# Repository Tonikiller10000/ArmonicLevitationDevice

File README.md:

# ArmonicLevitationDevice

## Description:
<table>
  <tr>
    <td> 
      This levitation device uses an NE555 with an TC78H621FNG Dual-Bridge driver to generate a 40KHz sine wave signal witch is sent back at the rigth distance to make zones of high and low pressure in witch it can trap small objects.
    </td>
    <td>
       </td>
  </tr>
</table>

<table>
  <tr>
    <td></td>
    <td></td>
    <td></td>
  </tr>
</table>

## Schematic:

## How/where to use:
It can be powered with a 9V battery. (5-15v operating voltage range) 
Because of it`s design, multiple tipes of transmiters/transducers can be used by bending the pins. 
To use it, you can use only one board/transmitter ans a close flat surface to reflect the wave. 
For a stronger hold, you can use another transmitter connected to the SP2 pins.

> [!IMPORTANT]
> Change the distance between the transmitter1 and the surface/transmitter2 to create the nodes and antinodes for the project to work.

<table>
  <tr>
    <td> 
    This king of technology, can be used in medical industry to observe and experiment with liquids without making contact with them.</td>
    <td></td>
  </tr>
</table>

## Links:
- TC78H621FNG datasheet (Dual-Bridge driver): https://toshiba.semicon-storage.com/info/TC78H621FNG_datasheet_en_20170410.pdf?did=57992&prodName=TC78H621FNG
- 78L05 datasheet (voltage regulator): https://www.sparkfun.com/datasheets/Components/LM7805.pdf
- NE555 datasheet (timer): https://pdf1.alldatasheet.com/datasheet-pdf/view/17972/PHILIPS/NE555.html
- Ultrasonic transducer: https://www.murata.com/-/media/webrenewal/products/sensor/ultrasonic/open/datasheet_maopn.ashx
- general transducers: https://tecsho.com/Download/Download/126816/fp

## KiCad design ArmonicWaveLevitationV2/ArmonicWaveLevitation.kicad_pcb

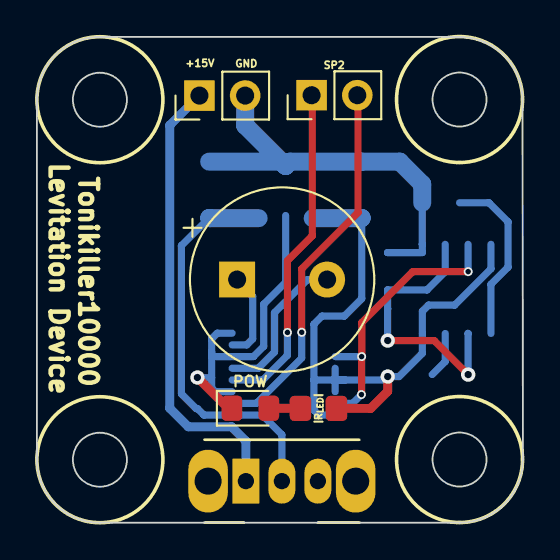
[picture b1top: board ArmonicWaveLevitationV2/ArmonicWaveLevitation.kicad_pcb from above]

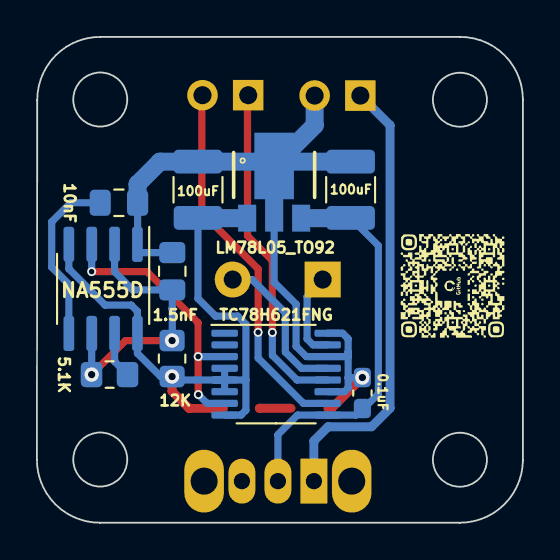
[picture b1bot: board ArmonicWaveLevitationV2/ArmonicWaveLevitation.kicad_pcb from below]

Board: 2 copper layers, 27.0 x 27.0 mm, 16 parts (10 on the bottom side), 13 nets.

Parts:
C1: 0.1uF; C_0603_1608Metric_Pad1.08x0.95mm_HandSolder
C2, C3: 100uF; C_1210_3225Metric_Pad1.33x2.70mm_HandSolder
C4: 10nF; C_0805_2012Metric_Pad1.18x1.45mm_HandSolder
C5: 1.5nF; C_0805_2012Metric_Pad1.18x1.45mm_HandSolder
D1: POW; D_0805_2012Metric_Pad1.15x1.40mm_HandSolder
J1: Batt conn; PinHeader_1x02_P2.54mm_Vertical
J6: SPK; PinHeader_1x02_P2.54mm_Vertical
LS1: TCT40-16_UltrasonicSpeaker; CP_Radial_D10.0mm_P5.00mm
R1: 5.1K; R_0805_2012Metric_Pad1.20x1.40mm_HandSolder
R2: 12K; R_0805_2012Metric_Pad1.20x1.40mm_HandSolder
R3: R_{LED}; R_0805_2012Metric_Pad1.20x1.40mm_HandSolder
SW1: POW; SW_CuK_OS102011MA1QN1_SPDT_Angled
U1: TC78H621FNG; TSSOP-16_4.4x5mm_P0.65mm
U2: LM78L05_TO92; PK(R-PSSO-F3)
U3: NA555D; SOIC-8_3.9x4.9mm_P1.27mm

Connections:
40KHz: U1.3 (PHA_A), U1.7 (PHA_B), U3.3 (Q)
+5V: C3.1, R2.2, R3.1, U1.4 (EN_A), U1.5 (VCC), U1.6 (~STBY), U1.8 (EN_B), U2.1 (VO), U3.4 (R), U3.8 (VCC)
+15V: C1.2, C2.1, SW1.2 (B), U1.9 (VM), U2.3 (VI)
GND: C1.1, C2.2, C3.2, C4.1, C5.1, D1.1 (K), J1.2, U1.11 (GND), U1.14 (GND), U1.16 (GND), U2.2 (GND), U3.1 (GND)
unnamed: D1.2 (A), R3.2
unnamed: J1.1, SW1.1 (A)
unnamed: J6.1, U1.12 (BO1)
unnamed: J6.2, U1.10 (BO2)
unnamed: LS1.1, U1.15 (AO1)
unnamed: LS1.2, U1.13 (AO2)
unnamed: C4.2, U3.5 (CV)
unnamed: R1.1, U3.7 (DIS)
unnamed: C5.2, R1.2, R2.1, U3.2 (TR), U3.6 (THR)

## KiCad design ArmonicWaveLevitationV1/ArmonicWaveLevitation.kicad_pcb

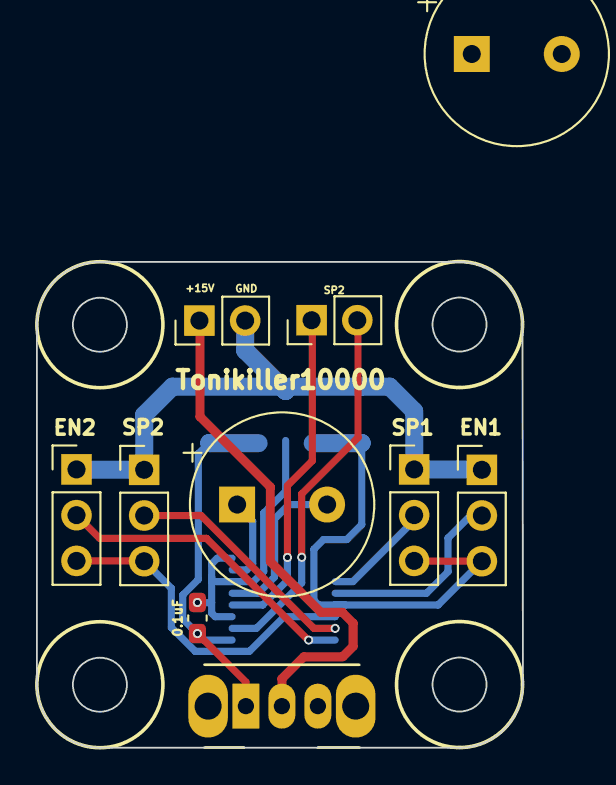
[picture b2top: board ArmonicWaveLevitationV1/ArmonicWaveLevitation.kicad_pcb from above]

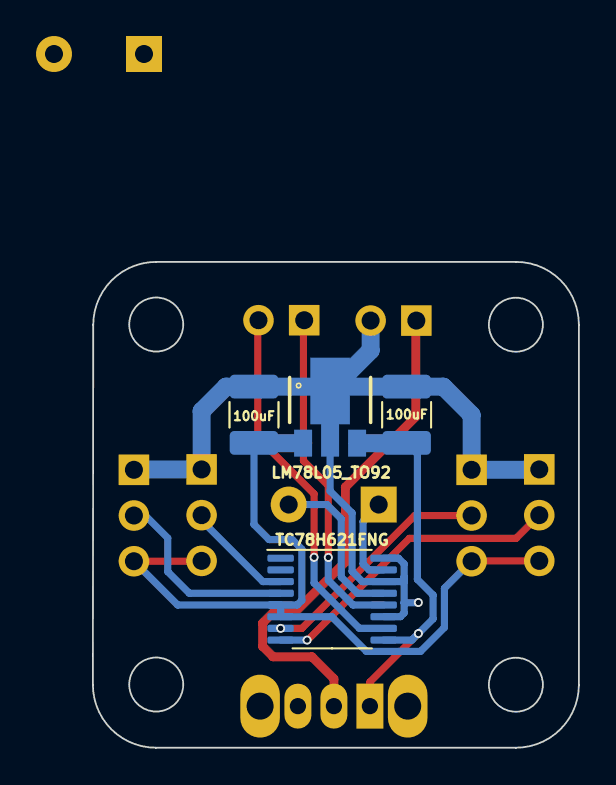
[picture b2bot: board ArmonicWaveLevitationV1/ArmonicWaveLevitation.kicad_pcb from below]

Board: 2 copper layers, 27.0 x 27.0 mm, 14 parts (4 on the bottom side), 12 nets.

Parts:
C1: 0.1uF; C_0603_1608Metric_Pad1.08x0.95mm_HandSolder
C2, C3: 100uF; C_1210_3225Metric_Pad1.33x2.70mm_HandSolder
J1: Battery connector; PinHeader_1x02_P2.54mm_Vertical
J2: SP1; PinHeader_1x03_P2.54mm_Vertical
J3: SP2; PinHeader_1x03_P2.54mm_Vertical
J4: EN1; PinHeader_1x03_P2.54mm_Vertical
J5: EN2; PinHeader_1x03_P2.54mm_Vertical
J6: SPK; PinHeader_1x02_P2.54mm_Vertical
LS1, LS2: TCT40-16_UltrasonicSpeaker; CP_Radial_D10.0mm_P5.00mm
SW1: POW; SW_CuK_OS102011MA1QN1_SPDT_Angled
U1: TC78H621FNG; TSSOP-16_4.4x5mm_P0.65mm
U2: LM78L05_TO92; PK(R-PSSO-F3)

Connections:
+5V: C3.1, J2.3, J3.3, J4.3, J5.3, U1.5 (VCC), U1.6 (~STBY), U2.1 (VO)
+15V: C1.2, C2.1, SW1.1 (A), U1.9 (VM), U2.3 (VI)
EN1: J4.2, U1.4 (EN_A)
EN2: J5.2, U1.8 (EN_B)
GND: C1.1, C2.2, C3.2, J1.2, J2.1, J3.1, J4.1, J5.1, U1.11 (GND), U1.14 (GND), U1.16 (GND), U2.2 (GND)
unnamed: J1.1, SW1.2 (B)
unnamed: J6.1, U1.12 (BO1)
unnamed: J6.2, U1.10 (BO2)
unnamed: LS1.1, U1.15 (AO1)
unnamed: LS1.2, U1.13 (AO2)
SP1: J2.2, U1.3 (PHA_A)
SP2: J3.2, U1.7 (PHA_B)

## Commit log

2024-02-27 upload
2024-02-27 upl2
2024-02-27 upd3
